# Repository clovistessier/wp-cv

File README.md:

# Waaave_Pool Eurorack CV Interface Module
The Waaave_Pool Eurorack CV Interface Module is a Eurorack module that allows you to use control voltage from a Eurorack modular synthesizer to modulate any of the 16 continuous parameters of the Waaave_Pool video synthesis system. Use CV from LFOs, sequencers, envelopes, S+H, and more to animate your video feedback. Used in conjuction with a conventional Eurorack synth patch, you can achieve nuanced syncing between your audio and video for a cohesive audiovisual performance. Due to the framebuffer based implementation of Waaave_Pool, the best visual results are using CV that changes at a speed lower than the framerate of the system.

## Revision B.
This version of the module connects directly to the GPIO pins of the Raspberry Pi 3B+ running Waaave_Pool. A limited run of these modules was produced and sold in August 2020. This version is intended to be used with LZX compatible eurorack modules and complies with the [LZX Patchable Video Standard](https://community.lzxindustries.net/t/the-lzx-patchable-video-standard/842) for "Animation Speed" CV (<30Hz), whereas +/-1V corresponds to +/-100% of the parameters range.
### Features
- 16 CV inputs expecting +/-1V (+/-12V tolerant)
- Bipolar attenuator aka attenuverter (-n to n) on each input
- Positive and Negative clipping for voltages outside the expected range
### Usage
All of the files required to build your own are included. You can upload the zipped gerber files to your PCB manufacturer of choice (JLCPCB has been used successfully in the past). Ordering an SMT stencil with the board is highly recommended due to the large quantity of SMD components. 

The KiCAD project files are also included, open the .pro file with KiCAD to view the project.

[Mouser Project Link](https://www.mouser.com/ProjectManager/ProjectDetail.aspx?AccessID=e002599eb7) for easy parts ordering. Don't forget the knobs and jacks from [Thonk](thonk.co.uk)!

The included front panel gerber files can be used to order an FR-4 front panel at the same time as the PCBs. You may get a follow up email from the PCB manufacturer since they assume that a PCB with no copper traces is probably unintentional.

To use the module with Waaave_Pool, you will need a 40-Pin IDC ribbon cable to connect betweent the header at the bottom of the module and the GPIO header of the Raspberry Pi. You will also need to be running a CV-compatible firmware version, which can be found all the way at the bottom of the [VSERPI Hardware and Images page](https://andreijaycreativecoding.com/VSERPI-hardware-and-images).

## Revision C. (WIP)
This version of the module incorporates an ESP32 microcontroller to handle the analog to digital conversion, and trasmits the information using [OSC](https://ccrma.stanford.edu/groups/osc/index.html) to Waaave_Pool over Ethernet and/or Wi-Fi. This version is intended to work with +/-5V control voltage, allowing for a much wider range of compatible CV sources from the Eurorack world, beyond just LZX. Due to the inherent flexibility of OSC, this module could also be used to send CV information to something other than Waaave_Pool, such as an application running on your computer. Development is still ongoing.

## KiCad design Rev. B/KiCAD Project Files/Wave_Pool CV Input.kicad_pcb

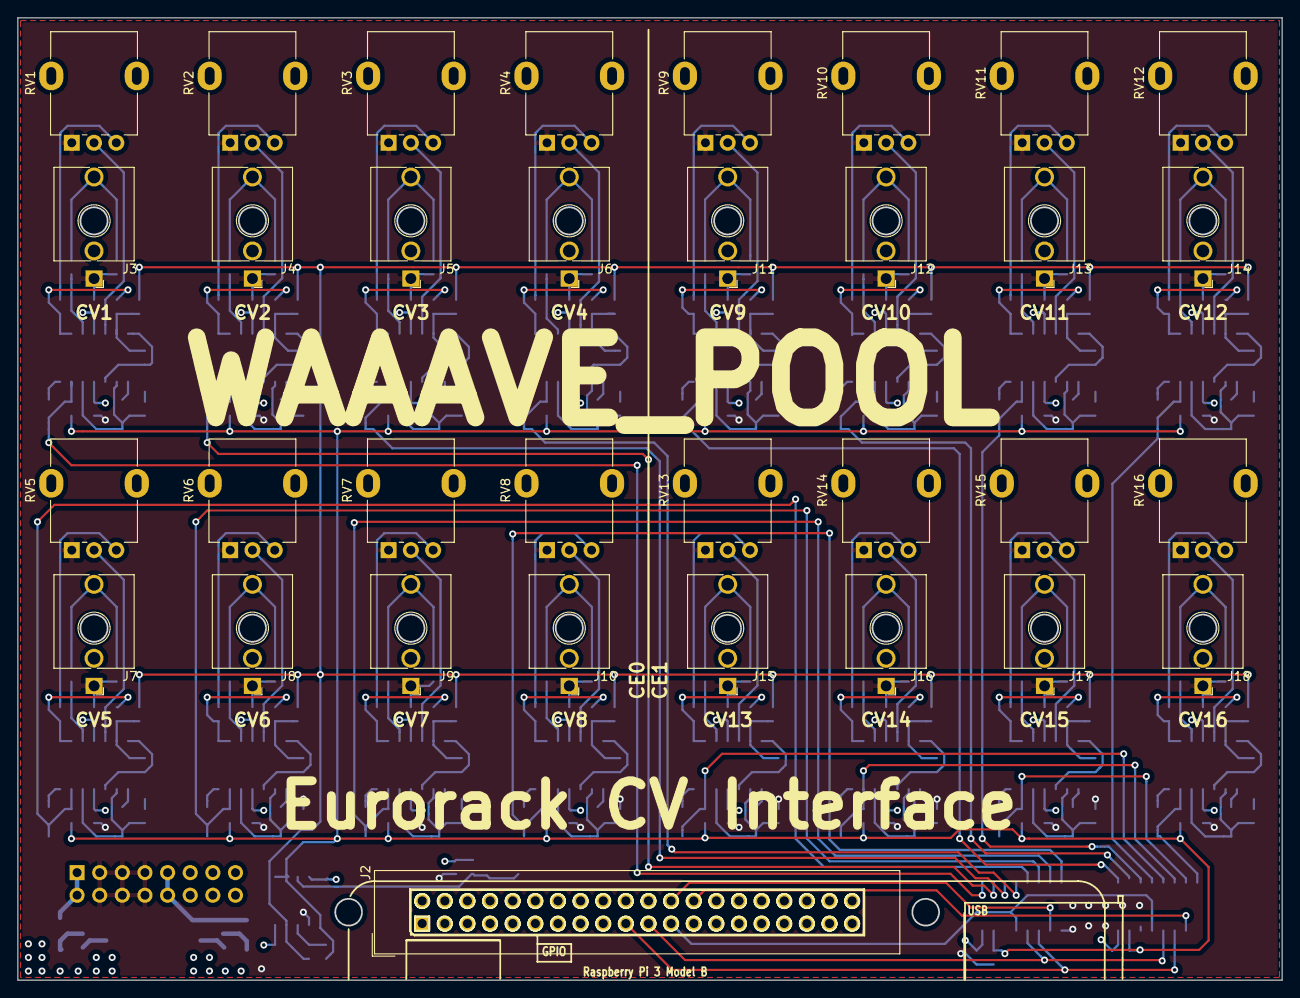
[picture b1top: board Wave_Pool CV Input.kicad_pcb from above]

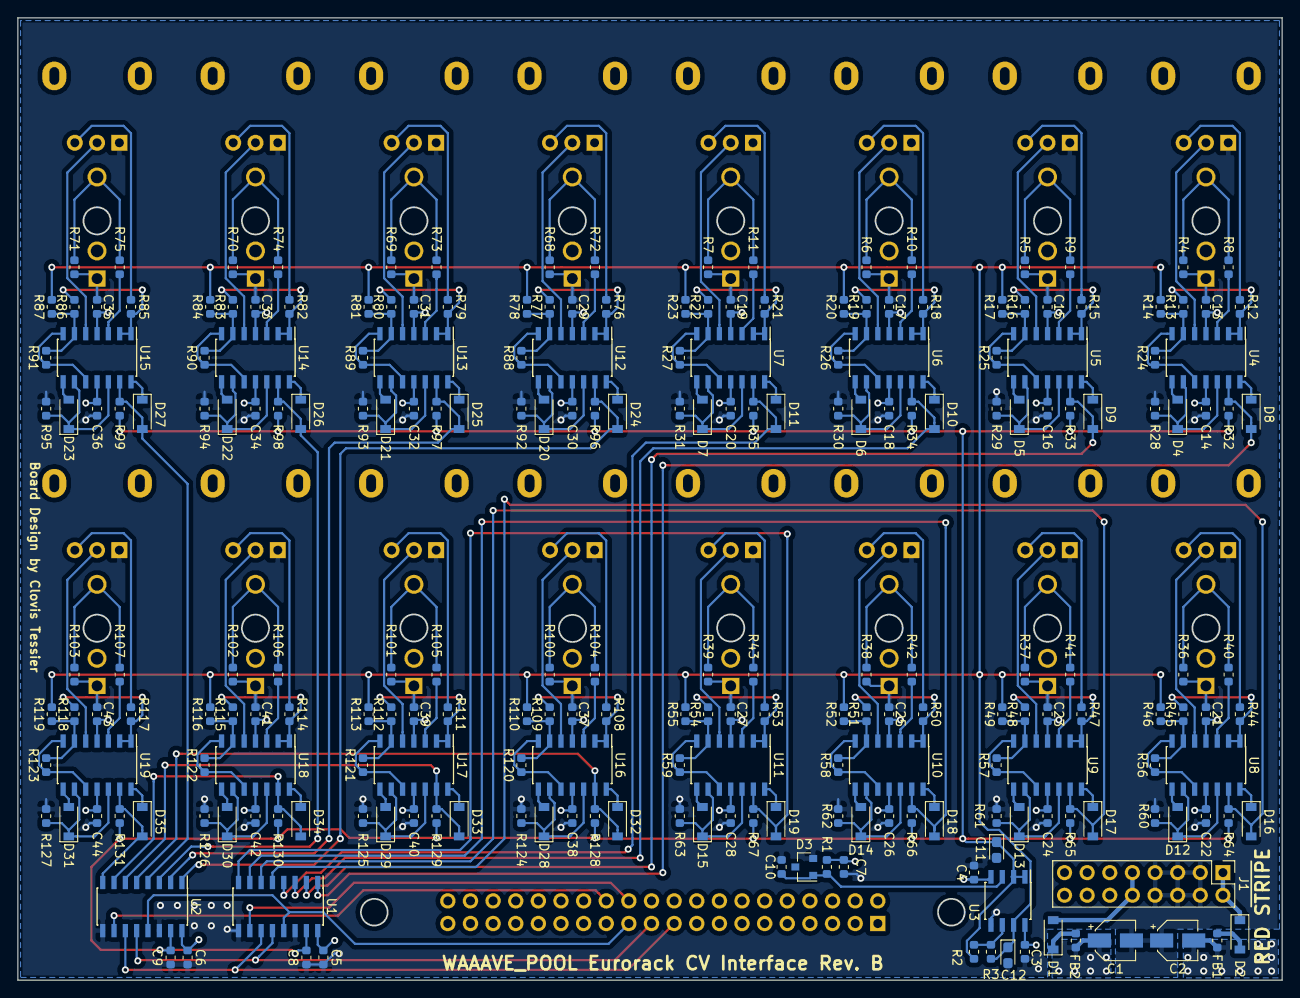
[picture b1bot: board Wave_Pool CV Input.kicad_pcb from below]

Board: 4 copper layers, 141.9 x 108.0 mm, 265 parts (232 on the bottom side), 193 nets.

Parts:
C1, C2: 10u 25V; CP_Elec_4x5.4
C3, C4, C5, C6, C8, C9, C13, C14, C15, C16, C17, C18, C19, C20, C21, C22, C23, C24, C25, C26, C27, C28, C29, C30, C31, C32, C33, C34, C35, C36, C37, C38, C39, C40, C41, C42, C43, C44: 100n; C_0603_1608Metric
C7, C10: 1u; C_0603_1608Metric
C11, C12: 10u; CP_EIA-2012-15_AVX-P
D1, D2: SM4001; D_SOD-123
D3: LM4040DBZ-2.0; SOT-23
D4, D5, D6, D7, D8, D9, D10, D11, D12, D13, D14, D15, D16, D17, D18, D19, D20, D21, D22, D23, D24, D25, D26, D27, D28, D29, D30, D31, D32, D33, D34, D35: 1N4148W; D_SOD-123
FB1, FB2: Ferrite_Bead; L_0603_1608Metric
J1: Eurorack_Power_Header_02x08_Hidden_Pins; PinHeader_2x08_P2.54mm_Vertical
J2: Raspberry_Pi_2_3; IDC-Header_2x20_P2.54mm_Vertical
J3, J4, J5, J6, J7, J8, J9, J10, J11, J12, J13, J14, J15, J16, J17, J18: Thonkiconn_Mono; Jack_3.5mm_QingPu_WQP-PJ398SM_Vertical_CircularHoles_Number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
R1, R2, R13, R14, R16, R17, R19, R20, R22, R23, R24, R25, R26, R27, R45, R46, R48, R49, R51, R52, R54, R55, R56, R57, R58, R59, R77, R78, R80, R81, R83, R84, R86, R87, R88, R89, R90, R91, R109, R110, R112, R113, R115, R116, R118, R119, R120, R121, R122, R123: 10K; R_0603_1608Metric
R3, R12, R15, R18, R21, R28, R29, R30, R31, R32, R33, R34, R35, R44, R47, R50, R53, R60, R61, R62, R63, R64, R65, R66, R67, R76, R79, R82, R85, R92, R93, R94, R95, R96, R97, R98, R99, R108, R111, R114, R117, R124, R125, R126, R127, R128, R129, R130, R131: 4.99K; R_0603_1608Metric
R4, R5, R6, R7, R36, R37, R38, R39, R68, R69, R70, R71, R100, R101, R102, R103: 100K; R_0603_1608Metric
R8, R9, R10, R11, R40, R41, R42, R43, R72, R73, R74, R75, R104, R105, R106, R107: 499R; R_0603_1608Metric
RV1, RV2, RV3, RV4, RV5, RV6, RV7, RV8, RV9, RV10, RV11, RV12, RV13, RV14, RV15, RV16: 10K; Potentiometer_Alpha_RD901F-40-00D_Single_Vertical
U1, U2: MCP3008; SOIC-16_3.9x9.9mm_P1.27mm
U3: TL072; SOIC-8_3.9x4.9mm_P1.27mm
U4, U5, U6, U7, U8, U9, U10, U11, U12, U13, U14, U15, U16, U17, U18, U19: TL074; SOIC-14_3.9x8.7mm_P1.27mm

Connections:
+3V3: C5.1, C6.1, J2.17, U1.16, U2.16
+12V: C1.1, C3.1, C7.1, C13.1, C15.1, C17.1, C19.1, C21.1, C23.1, C25.1, C27.1, C29.1, C31.1, C33.1, C35.1, C37.1, C39.1, C41.1, C43.1, FB2.1, R1.2, U3.8, U4.4, U5.4, U6.4, U7.4, U8.4, U9.4, U10.4, U11.4, U12.4, U13.4, U14.4, U15.4, U16.4, U17.4, U18.4, U19.4
-12V: C2.2, C4.2, C14.2, C16.2, C18.2, C20.2, C22.2, C24.2, C26.2, C28.2, C30.2, C32.2, C34.2, C36.2, C38.2, C40.2, C42.2, C44.2, FB1.1, U3.4, U4.11, U5.11, U6.11, U7.11, U8.11, U9.11, U10.11, U11.11, U12.11, U13.11, U14.11, U15.11, U16.11, U17.11, U18.11, U19.11
/CV Input 1-4/CV1: D8.2, R32.2, U1.1, U4.13
/CV Input 1-4/CV2: D9.2, R33.2, U1.2, U5.13
/CV Input 1-4/CV3: D10.2, R34.2, U1.3, U6.13
/CV Input 1-4/CV4: D11.2, R35.2, U1.4, U7.13
/CV Input 5-8/CV5: D16.2, R64.2, U1.5, U8.13
/CV Input 5-8/CV6: D17.2, R65.2, U1.6, U9.13
/CV Input 5-8/CV7: D18.2, R66.2, U1.7, U10.13
/CV Input 5-8/CV8: D19.2, R67.2, U1.8, U11.13
/CV Input 9-12/CV9: D24.2, R96.2, U2.1, U12.13
/CV Input 9-12/CV10: D25.2, R97.2, U2.2, U13.13
/CV Input 9-12/CV11: D26.2, R98.2, U2.3, U14.13
/CV Input 9-12/CV12: D27.2, R99.2, U2.4, U15.13
/CV Input 13-16/CV13: D32.2, R128.2, U2.5, U16.13
/CV Input 13-16/CV14: D33.2, R129.2, U2.6, U17.13
/CV Input 13-16/CV15: D34.2, R130.2, U2.7, U18.13
/CV Input 13-16/CV16: D35.2, R131.2, U2.8, U19.13
/SPI_CE0: J2.24, U1.10
/SPI_CE1: J2.26, U2.10
/SPI_CLK: J2.23, U1.13, U2.13
/SPI_MISO: J2.21, U1.12, U2.12
/SPI_MOSI: J2.19, U1.11, U2.11
/VREF_UNBUFFERED: C10.1, D3.1, R1.1, U3.3
DC_Offset: C12.1, R3.1, R14.2, R17.2, R20.2, R23.2, R46.2, R49.2, R52.2, R55.2, R78.2, R81.2, R84.2, R87.2, R110.2, R113.2, R116.2, R119.2, U3.7
GND: C1.2, C2.1, C3.2, C4.1, C5.2, C6.2, C7.2, C8.2, C9.2, C10.2, C11.2, C12.2, C13.2, C14.1, C15.2, C16.1, C17.2, C18.1, C19.2, C20.1, C21.2, C22.1, C23.2, C24.1, C25.2, C26.1, C27.2, C28.1, C29.2, C30.1, C31.2, C32.1, C33.2, C34.1, C35.2, C36.1, C37.2, C38.1, C39.2, C40.1, C41.2, C42.1, C43.2, C44.1, D3.2, J1.3, J1.4, J1.5, J1.6, J1.7, J1.8, J2.25, J3.1, J4.1, J5.1, J6.1, J7.1, J8.1, J9.1, J10.1, J11.1, J12.1, J13.1, J14.1, J15.1, J16.1, J17.1, J18.1, R4.2, R5.2, R6.2, R7.2, R28.1, R29.1, R30.1, R31.1, R36.2, R37.2, R38.2, R39.2, R60.1, R61.1, R62.1, R63.1, R68.2, R69.2, R70.2, R71.2, R92.1, R93.1, R94.1, R95.1, R100.2, R101.2, R102.2, R103.2, R124.1, R125.1, R126.1, R127.1, RV1.1, RV2.1, RV3.1, RV4.1, RV5.1, RV6.1, RV7.1, RV8.1, RV9.1, RV10.1, RV11.1, RV12.1, RV13.1, RV14.1, RV15.1, RV16.1, U1.9, U1.14, U2.9, U2.14, U3.5
unnamed: D1.1, FB2.2
unnamed: D1.2, J1.9, J1.10
unnamed: D2.1, J1.1, J1.2
unnamed: D2.2, FB1.2
unnamed: D4.1, R28.2, U4.9, U4.12
unnamed: D4.2, U4.8
unnamed: D5.1, R29.2, U5.9, U5.12
unnamed: D5.2, U5.8
unnamed: D6.1, R30.2, U6.9, U6.12
unnamed: D6.2, U6.8
unnamed: D7.1, R31.2, U7.9, U7.12
unnamed: D7.2, U7.8
unnamed: D8.1, U4.14
unnamed: D9.1, U5.14
unnamed: D10.1, U6.14
unnamed: D11.1, U7.14
unnamed: D12.1, R60.2, U8.9, U8.12
unnamed: D12.2, U8.8
unnamed: D13.1, R61.2, U9.9, U9.12
unnamed: D13.2, U9.8
unnamed: D14.1, R62.2, U10.9, U10.12
unnamed: D14.2, U10.8
unnamed: D15.1, R63.2, U11.9, U11.12
unnamed: D15.2, U11.8
unnamed: D16.1, U8.14
unnamed: D17.1, U9.14
unnamed: D18.1, U10.14
unnamed: D19.1, U11.14
unnamed: D20.1, R92.2, U12.9, U12.12
unnamed: D20.2, U12.8
unnamed: D21.1, R93.2, U13.9, U13.12
unnamed: D21.2, U13.8
unnamed: D22.1, R94.2, U14.9, U14.12
unnamed: D22.2, U14.8
unnamed: D23.1, R95.2, U15.9, U15.12
unnamed: D23.2, U15.8
unnamed: D24.1, U12.14
unnamed: D25.1, U13.14
unnamed: D26.1, U14.14
unnamed: D27.1, U15.14
unnamed: D28.1, R124.2, U16.9, U16.12
unnamed: D28.2, U16.8
unnamed: D29.1, R125.2, U17.9, U17.12
unnamed: D29.2, U17.8
unnamed: D30.1, R126.2, U18.9, U18.12
unnamed: D30.2, U18.8
unnamed: D31.1, R127.2, U19.9, U19.12
unnamed: D31.2, U19.8
unnamed: D32.1, U16.14
unnamed: D33.1, U17.14
unnamed: D34.1, U18.14
unnamed: D35.1, U19.14
unnamed: J3.3, R4.1, R8.2
unnamed: J4.3, R5.1, R9.2
unnamed: J5.3, R6.1, R10.2
unnamed: J6.3, R7.1, R11.2
unnamed: J7.3, R36.1, R40.2
unnamed: J8.3, R37.1, R41.2
unnamed: J9.3, R38.1, R42.2
unnamed: J10.3, R39.1, R43.2
unnamed: J11.3, R68.1, R72.2
unnamed: J12.3, R69.1, R73.2
unnamed: J13.3, R70.1, R74.2
unnamed: J14.3, R71.1, R75.2
unnamed: J15.3, R100.1, R104.2
unnamed: J16.3, R101.1, R105.2
unnamed: J17.3, R102.1, R106.2
unnamed: J18.3, R103.1, R107.2
unnamed: R2.1, R3.2, U3.6
unnamed: R8.1, U4.3
unnamed: R9.1, U5.3
unnamed: R10.1, U6.3
unnamed: R11.1, U7.3
unnamed: R12.1, RV1.3
unnamed: R12.2, R13.2, U4.1, U4.2
unnamed: R13.1, R14.1, R24.2, U4.6
unnamed: R15.1, RV2.3
unnamed: R15.2, R16.2, U5.1, U5.2
unnamed: R16.1, R17.1, R25.2, U5.6
unnamed: R18.1, RV3.3
unnamed: R18.2, R19.2, U6.1, U6.2
unnamed: R19.1, R20.1, R26.2, U6.6
unnamed: R21.1, RV4.3
unnamed: R21.2, R22.2, U7.1, U7.2
unnamed: R22.1, R23.1, R27.2, U7.6
unnamed: R24.1, U4.7, U4.10
unnamed: R25.1, U5.7, U5.10
unnamed: R26.1, U6.7, U6.10
unnamed: R27.1, U7.7, U7.10
unnamed: R40.1, U8.3
unnamed: R41.1, U9.3
unnamed: R42.1, U10.3
unnamed: R43.1, U11.3
unnamed: R44.1, RV5.3
unnamed: R44.2, R45.2, U8.1, U8.2
unnamed: R45.1, R46.1, R56.2, U8.6
unnamed: R47.1, RV6.3
unnamed: R47.2, R48.2, U9.1, U9.2
unnamed: R48.1, R49.1, R57.2, U9.6
unnamed: R50.1, RV7.3
unnamed: R50.2, R51.2, U10.1, U10.2
unnamed: R51.1, R52.1, R58.2, U10.6
unnamed: R53.1, RV8.3
unnamed: R53.2, R54.2, U11.1, U11.2
unnamed: R54.1, R55.1, R59.2, U11.6
unnamed: R56.1, U8.7, U8.10
unnamed: R57.1, U9.7, U9.10
unnamed: R58.1, U10.7, U10.10
unnamed: R59.1, U11.7, U11.10
unnamed: R72.1, U12.3
unnamed: R73.1, U13.3
unnamed: R74.1, U14.3
unnamed: R75.1, U15.3
unnamed: R76.1, RV9.3
unnamed: R76.2, R77.2, U12.1, U12.2
unnamed: R77.1, R78.1, R88.2, U12.6
unnamed: R79.1, RV10.3
unnamed: R79.2, R80.2, U13.1, U13.2
unnamed: R80.1, R81.1, R89.2, U13.6
unnamed: R82.1, RV11.3
unnamed: R82.2, R83.2, U14.1, U14.2
unnamed: R83.1, R84.1, R90.2, U14.6
unnamed: R85.1, RV12.3
unnamed: R85.2, R86.2, U15.1, U15.2
unnamed: R86.1, R87.1, R91.2, U15.6
unnamed: R88.1, U12.7, U12.10
unnamed: R89.1, U13.7, U13.10
unnamed: R90.1, U14.7, U14.10
unnamed: R91.1, U15.7, U15.10
unnamed: R104.1, U16.3
unnamed: R105.1, U17.3
unnamed: R106.1, U18.3
unnamed: R107.1, U19.3
unnamed: R108.1, RV13.3
unnamed: R108.2, R109.2, U16.1, U16.2
unnamed: R109.1, R110.1, R120.2, U16.6
unnamed: R111.1, RV14.3
unnamed: R111.2, R112.2, U17.1, U17.2
unnamed: R112.1, R113.1, R121.2, U17.6
unnamed: R114.1, RV15.3
unnamed: R114.2, R115.2, U18.1, U18.2
unnamed: R115.1, R116.1, R122.2, U18.6
unnamed: R117.1, RV16.3
unnamed: R117.2, R118.2, U19.1, U19.2
unnamed: R118.1, R119.1, R123.2, U19.6
unnamed: R120.1, U16.7, U16.10
unnamed: R121.1, U17.7, U17.10
unnamed: R122.1, U18.7, U18.10
unnamed: R123.1, U19.7, U19.10
unnamed: RV1.2, U4.5
unnamed: RV2.2, U5.5
unnamed: RV3.2, U6.5
unnamed: RV4.2, U7.5
unnamed: RV5.2, U8.5
unnamed: RV6.2, U9.5
unnamed: RV7.2, U10.5
unnamed: RV8.2, U11.5
unnamed: RV9.2, U12.5
unnamed: RV10.2, U13.5
unnamed: RV11.2, U14.5
unnamed: RV12.2, U15.5
unnamed: RV13.2, U16.5
unnamed: RV14.2, U17.5
unnamed: RV15.2, U18.5
unnamed: RV16.2, U19.5
Vref: C8.1, C9.1, C11.1, R2.2, R32.1, R33.1, R34.1, R35.1, R64.1, R65.1, R66.1, R67.1, R96.1, R97.1, R98.1, R99.1, R128.1, R129.1, R130.1, R131.1, U1.15, U2.15, U3.1, U3.2

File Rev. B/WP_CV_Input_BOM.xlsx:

Reference | Quantity | Value | Footprint | Vendor | Mouser P/N | Price | Ext. Price | Website | Description
C1 C2 | 2 | 10u 25V | Capacitor_THT:CP_Radial_D5.0mm_P2.00mm | Mouser | 667-ECE-A1VKS100 | 0.28000000000000003 | 0.56000000000000005 | https://www.mouser.com/ProductDetail/667-ECE-A1VKS100 | Aluminum Electrolytic Capacitors - Radial Leaded 10UF 35V KS RADIAL
C11 C12 | 2 | 10u | Capacitor_Tantalum_SMD:CP_EIA-2012-15_AVX-P | Mouser | 74-TMCP0J106MTRF | 0.36 | 0.72 | https://www.mouser.com/ProductDetail/74-TMCP0J106MTRF | Tantalum Capacitors - Solid SMD 7volts 10uF 20% Molded Case, 0805
C13 C14 C15 C16 C17 C18 C19 C20 C21 C22 C23 C24 C25 C26 C27 C28 C29 C3 C30 C31 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 | 38 | 100n | Capacitor_SMD:C_0603_1608Metric | Mouser | 80-C0603C104Z3V | 3.2000000000000001E-2 | 1.216 | https://www.mouser.com/ProductDetail/80-C0603C104Z3V | Multilayer Ceramic Capacitors MLCC - SMD/SMT 25V 0.1uF 0603 Y5V -20/+80%
C10 C7 | 2 | 1u | Capacitor_SMD:C_0603_1608Metric | Mouser | 80-C0603C105K9P | 0.1 | 0.2 | https://www.mouser.com/ProductDetail/80-C0603C105K9P | Multilayer Ceramic Capacitors MLCC - SMD/SMT 1uF 16.0V
D1 D2 | 2 | SM4001 | Diode_SMD:D_SOD-123 | Mouser | 833-SM4001PL-TP | 0.2 | 0.4 | https://www.mouser.com/ProductDetail/833-SM4001PL-TP | Rectifiers Standard 50V 1A
D3 | 1 | LM4040DBZ-2.0 | Package_TO_SOT_SMD:SOT-23 | Mouser | 700-LM4040AEM3-2.1T | 2.36 | 2.36 | https://www.mouser.com/ProductDetail/700-LM4040AEM3-2.1T | Voltage References Improved Precision Micropower Shunt Voltage Reference with M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
D10 D11 D12 D13 D14 D15 D16 D17 D18 D19 D20 D21 D22 D23 D24 D25 D26 D27 D28 D29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 | 32 | 1N4148W | Diode_SMD:D_SOD-123 | Mouser | 621-1N4148W-F | 0.16 | 5.12 | https://www.mouser.com/ProductDetail/621-1N4148W-F | Diodes - General Purpose, Power, Switching SURFACE MOUNT FAST SWITCHING DIODE
FB1 FB2 | 2 | Ferrite_Bead | Inductor_SMD:L_0603_1608Metric | Mouser | 875-MI0603J680R-10 | 0.1 | 0.2 | https://www.mouser.com/ProductDetail/875-MI0603J680R-10 | Ferrite Beads 68ohms 100MHz 1A Monolithic 0603 SMD
J1 | 1 | Eurorack_Power_Header_02x08 | Connector_PinHeader_2.54mm:PinHeader_2x08_P2.54mm_Vertical | Mouser | 649-1012938191601BLF | 0.48 | 0.48 | https://www.mouser.com/ProductDetail/649-1012938191601BLF | Headers & Wire Housings ECONOSTIK HEADER DR VT TH 2X8
J2 | 1 | Raspberry_Pi_2_3_GPIO_Header | Connector_PinHeader_2.54mm:PinHeader_2x20_P2.54mm_Vertical | Mouser | 649-1012938194002BLF | 1.1100000000000001 | 1.1100000000000001 | https://www.mouser.com/ProductDetail/649-1012938194002BLF | Headers & Wire Housings ECONOSTIK HEADER DR VT TH 2X20
R1 R109 R110 R112 R113 R115 R116 R118 R119 R120 R121 R122 R123 R13 R14 R16 R17 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 | 50 | 10K | Resistor_SMD:R_0603_1608Metric | Mouser | 667-ERJ-3EKF1002V | 0.05 | 2.5 | https://www.mouser.com/ProductDetail/667-ERJ-3EKF1002V | Thick Film Resistors - SMD 0603 10Kohms 1% AEC-Q200
R124 R125 R126 R127 R128 R129 R130 R131 R28 R29 R30 R31 R32 R33 R34 R35 R60 R61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 | 32 | 1K | Resistor_SMD:R_0603_1608Metric | Mouser | 667-ERJ-PA3F1001V | 0.06 | 1.92 | https://www.mouser.com/ProductDetail/667-ERJ-PA3F1001V | Thick Film Resistors - SMD 0603 1Kohm 1% Anti-Surge AEC-Q200
R108 R111 R114 R117 R12 R15 R18 R21 R3 R44 R47 R50 R53 R76 R79 R82 R85 | 17 | 4.99K | Resistor_SMD:R_0603_1608Metric | Mouser | 603-RC0603FR-104K99L | 0.02 | 0.34 | https://www.mouser.com/ProductDetail/603-RC0603FR-104K99L | Thick Film Resistors - SMD 4.99K ohm 1% 75V General Purpose
R100 R101 R102 R103 R36 R37 R38 R39 R4 R5 R6 R68 R69 R7 R70 R71 | 16 | 100K | Resistor_SMD:R_0603_1608Metric | Mouser | 603-RC0603FR-07100KL | 0.02 | 0.32 | https://www.mouser.com/ProductDetail/603-RC0603FR-07100KL | Thick Film Resistors - SMD 100K OHM 1%
R10 R104 R105 R106 R107 R11 R40 R41 R42 R43 R72 R73 R74 R75 R8 R9 | 16 | 499R | Resistor_SMD:R_0603_1608Metric | Mouser | 71-CRCW0603-499-E3 | 0.03 | 0.48 | https://www.mouser.com/ProductDetail/71-CRCW0603-499-E3 | Thick Film Resistors - SMD 1/10watt 499ohms 1%
U1 U2 | 2 | MCP3008 | Package_SO:SOIC-16_3.9x9.9mm_P1.27mm | Mouser | 579-MCP3008T-I/SL | 2.19 | 4.38 | https://www.mouser.com/ProductDetail/579-MCP3008T-I-SL | Analog to Digital Converters - ADC 10-bit SPI 8 Chl IND TEMP, SOIC16
U3 | 1 | TL072 | Package_SO:SOIC-8_3.9x4.9mm_P1.27mm | Mouser | 595-TL072CDR | 0.41 | 0.41 | https://www.mouser.com/ProductDetail/595-TL072CDR | Operational Amplifiers - Op Amps Dual JFET Op Amp
U10 U11 U12 U13 U14 U15 U16 U17 U18 U19 U4 U5 U6 U7 U8 U9 | 16 | TL074 | Package_SO:SOIC-14_3.9x8.7mm_P1.27mm | Mouser | 511-TL074IDT | 0.48 | 7.68 | https://www.mouser.com/ProductDetail/511-TL074IDT | Operational Amplifiers - Op Amps Quad Low Noise JFET
J10 J11 J12 J13 J14 J15 J16 J17 J18 J3 J4 J5 J6 J7 J8 J9 | 16 | Thonkiconn_Mono | Connector_Audio_Extra:Jack_3.5mm_QingPu_WQP-PJ398SM_Vertical_CircularHoles_Numb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 | Thonk |  | 0.43 | 6.88 | https://www.thonk.co.uk/shop/thonkiconn/ | Thonkiconn Mono 3.5mm Audio Jack
RV1 RV10 RV11 RV12 RV13 RV14 RV15 RV16 RV2 RV3 RV4 RV5 RV6 RV7 RV8 RV9 | 16 | B10K Center Detent | Potentiometer_THT_Extra:Potentiometer_Alpha_RD901F-40-00D_Single_Vertical_Circu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 | Thonk |  | 1.04 | 16.64 | https://www.thonk.co.uk/shop/ttpots/ | Song Huei 9mm Tall Trimmer Potentiometer
 |  |  |  |  |  | Total Price: | 53.916000000000004
 |  |  |  |  |  |  |  | Mouser Project Page:
 |  |  |  |  |  |  |  | https://www.mouser.com/ProjectManager/ProjectDetail.aspx?Acc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

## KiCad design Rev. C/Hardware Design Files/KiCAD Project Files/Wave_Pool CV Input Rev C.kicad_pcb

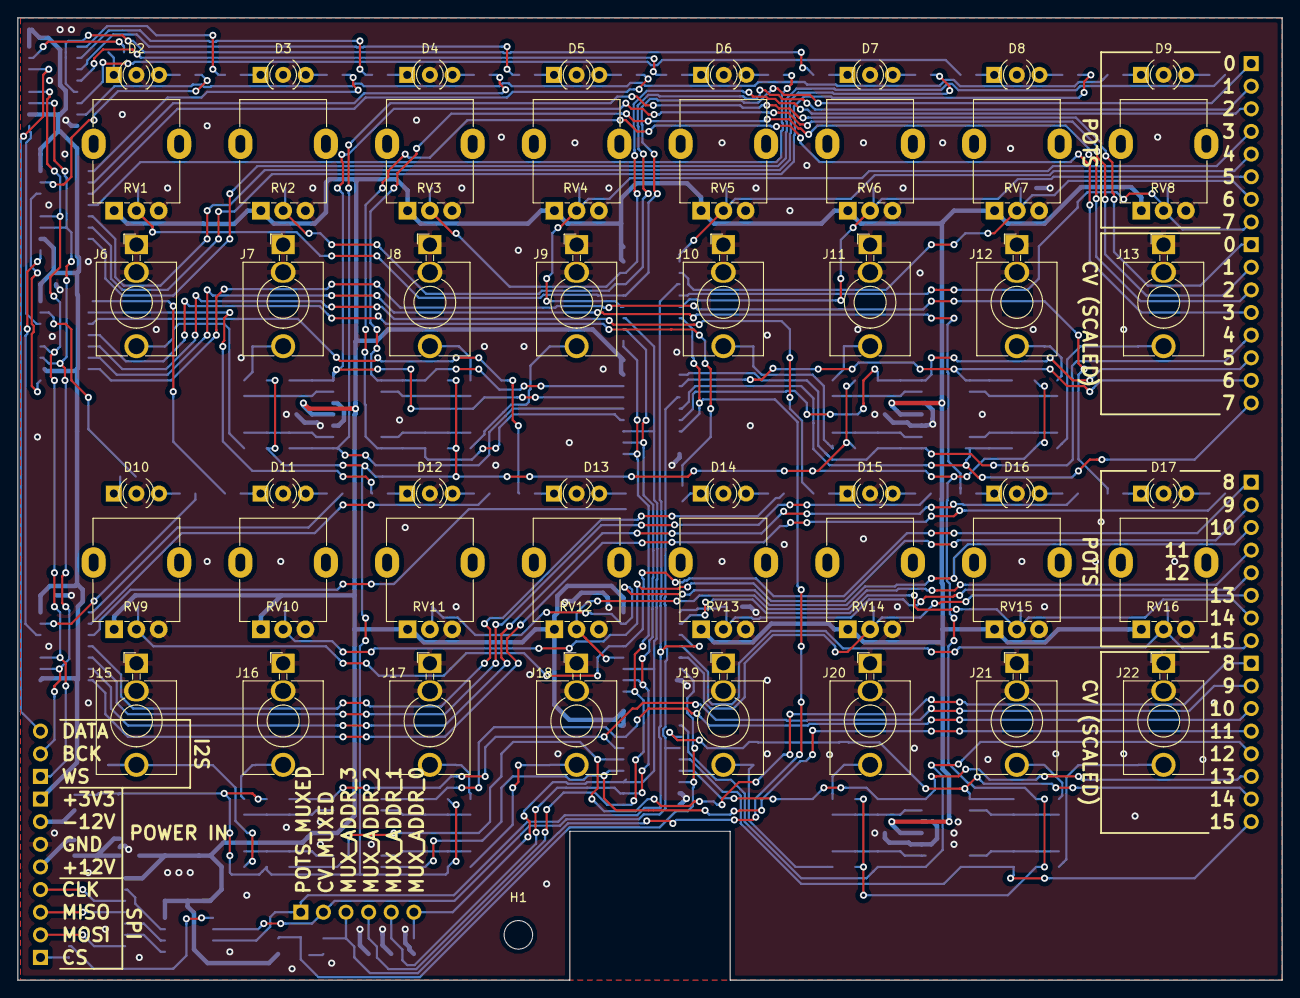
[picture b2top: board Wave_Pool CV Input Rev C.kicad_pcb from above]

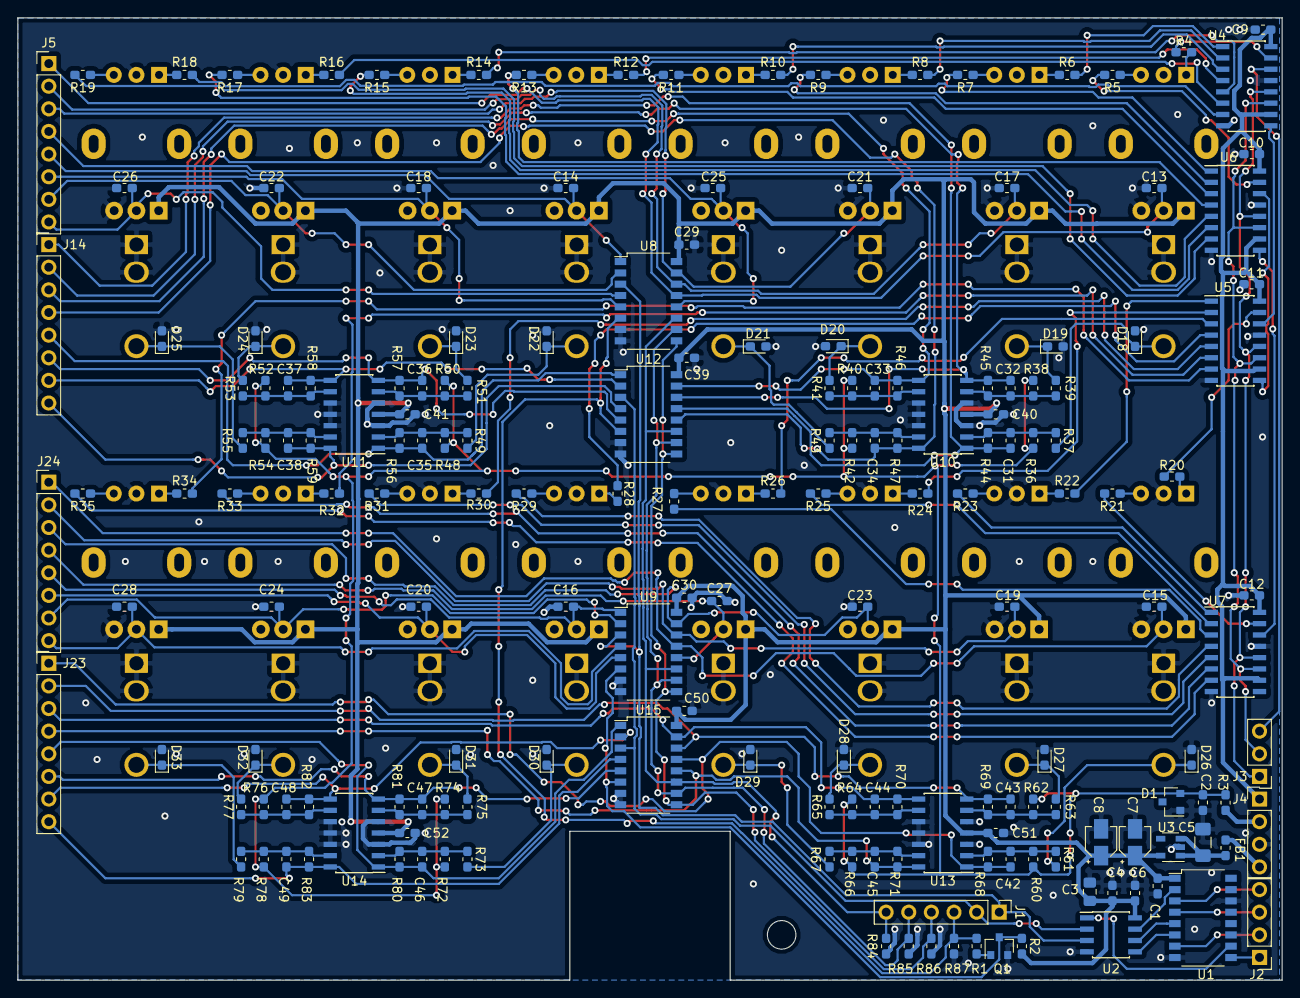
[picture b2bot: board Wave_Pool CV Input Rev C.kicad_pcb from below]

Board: 2 copper layers, 141.9 x 108.0 mm, 230 parts (181 on the bottom side), 157 nets.

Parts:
C1, C6, C9, C10, C11, C12, C13, C14, C15, C16, C17, C18, C19, C20, C21, C22, C23, C24, C25, C26, C27, C28, C29, C30, C39, C40, C41, C50, C51, C52: 100n; C_0603_1608Metric_Pad1.05x0.95mm_HandSolder
C2, C4: 1u; C_0603_1608Metric_Pad1.05x0.95mm_HandSolder
C3: 10u; C_0805_2012Metric_Pad1.15x1.40mm_HandSolder
C5: 22u; C_1206_3216Metric_Pad1.42x1.75mm_HandSolder
C7, C8: 10u; CP_Elec_3x5.4
C31, C32, C33, C34, C35, C36, C37, C38, C42, C43, C44, C45, C46, C47, C48, C49: 1n; C_0603_1608Metric_Pad1.05x0.95mm_HandSolder
D1: LM4040DBZ-10; SOT-23
D2, D3, D4, D5, D6, D7, D8, D9, D10, D11, D12, D13, D14, D15, D16, D17: Kingbright W115WSURKMGKW; LED_D3.0mm-3
D18, D19, D20, D21, D22, D23, D24, D25, D26, D27, D28, D29, D30, D31, D32, D33: D_TVS; D_0603_1608Metric_Pad1.05x0.95mm_HandSolder
FB1: Ferrite_Bead; L_0603_1608Metric_Pad1.05x0.95mm_HandSolder
H1: MountingHole; MountingHole_3.2mm_M3
J1: Conn_01x06; PinHeader_1x06_P2.54mm_Vertical
J2, J4: Conn_01x04; PinHeader_1x04_P2.54mm_Vertical
J3: Conn_01x03; PinHeader_1x03_P2.54mm_Vertical
J5, J14, J23, J24: Conn_01x08; PinHeader_1x08_P2.54mm_Vertical
J6, J7, J8, J9, J10, J11, J12, J13, J15, J16, J17, J18, J19, J20, J21, J22: Thonkiconn_Mono; Jack_3.5mm_Thonkiconn_Mono
Q1: MMBT3904; SOT-23
R1, R2, R84, R85, R86, R87: 10k; R_0603_1608Metric_Pad1.05x0.95mm_HandSolder
R3, R4, R6, R8, R10, R12, R14, R16, R18, R20, R22, R24, R26, R28, R30, R32, R34: 2.4k; R_0603_1608Metric_Pad1.05x0.95mm_HandSolder
R5, R7, R9, R11, R13, R15, R17, R19, R21, R23, R25, R27, R29, R31, R33, R35: 1.5k; R_0603_1608Metric_Pad1.05x0.95mm_HandSolder
R36, R38, R40, R42, R48, R50, R52, R54, R60, R62, R64, R66, R72, R74, R76, R78: 200k; R_0603_1608Metric_Pad1.05x0.95mm_HandSolder
R37, R39, R41, R43, R49, R51, R53, R55, R61, R63, R65, R67, R73, R75, R77, R79: 100k; R_0603_1608Metric_Pad1.05x0.95mm_HandSolder
R44, R45, R46, R47, R56, R57, R58, R59, R68, R69, R70, R71, R80, R81, R82, R83: 33k; R_0603_1608Metric_Pad1.05x0.95mm_HandSolder
RV1, RV2, RV3, RV4, RV5, RV6, RV7, RV8, RV9, RV10, RV11, RV12, RV13, RV14, RV15, RV16: R_POT_US; Potentiometer_Alpha_9mm_Single_Vertical
U1: 4050; SOP-16_4.4x10.4mm_P1.27mm
U2: MCP3202; SOIC-8_3.9x4.9mm_P1.27mm
U3: LD2981ABM33TR; SOT-23-5
U4, U5, U6, U7: 74HC595; SOIC-16_3.9x9.9mm_P1.27mm
U8, U9, U12, U15: 4051; SOP-16_4.4x10.4mm_P1.27mm
U10, U11, U13, U14: MCP6004; SOIC-14_3.9x8.7mm_P1.27mm

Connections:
+3.3VA: C1.1, C3.1, C4.1, C6.1, C7.1, C8.1, C29.1, C30.1, C39.1, C40.1, C41.1, C50.1, C51.1, C52.1, R2.2, RV1.1, RV2.1, RV3.1, RV4.1, RV5.1, RV6.1, RV7.1, RV8.1, RV9.1, RV10.1, RV11.1, RV12.1, RV13.1, RV14.1, RV15.1, RV16.1, U1.1, U2.8, U3.5, U8.16, U9.16, U10.4, U11.4, U12.16, U13.4, U14.4, U15.16
+3V3: C9.1, C10.1, C11.1, C12.1, J4.1, U4.10, U4.16, U5.10, U5.16, U6.10, U6.16, U7.10, U7.16
+12V: FB1.2, J4.4
-12V: J4.2, R3.1
/ATTENUVERTER_POTS/CV_ATT_0: C13.1, J5.1, RV1.2, U8.13
/ATTENUVERTER_POTS/CV_ATT_1: C17.1, J5.2, RV2.2, U8.14
/ATTENUVERTER_POTS/CV_ATT_2: C21.1, J5.3, RV3.2, U8.15
/ATTENUVERTER_POTS/CV_ATT_3: C25.1, J5.4, RV4.2, U8.12
/ATTENUVERTER_POTS/CV_ATT_4: C14.1, J5.5, RV5.2, U8.1
/ATTENUVERTER_POTS/CV_ATT_5: C18.1, J5.6, RV6.2, U8.5
/ATTENUVERTER_POTS/CV_ATT_6: C22.1, J5.7, RV7.2, U8.2
/ATTENUVERTER_POTS/CV_ATT_7: C26.1, J5.8, RV8.2, U8.4
/ATTENUVERTER_POTS/CV_ATT_8: C15.1, J24.1, RV9.2, U9.13
/ATTENUVERTER_POTS/CV_ATT_9: C19.1, J24.2, RV10.2, U9.14
/ATTENUVERTER_POTS/CV_ATT_10: C23.1, J24.3, RV11.2, U9.15
/ATTENUVERTER_POTS/CV_ATT_11: C27.1, J24.4, RV12.2, U9.12
/ATTENUVERTER_POTS/CV_ATT_12: C16.1, J24.5, RV13.2, U9.1
/ATTENUVERTER_POTS/CV_ATT_13: C20.1, J24.6, RV14.2, U9.5
/ATTENUVERTER_POTS/CV_ATT_14: C24.1, J24.7, RV15.2, U9.2
/ATTENUVERTER_POTS/CV_ATT_15: C28.1, J24.8, RV16.2, U9.4
/CV_ATT_MUXED: J1.1, U2.3, U8.3, U9.3
/CV_INPUTS/CV_INPUTS_BOTTOM_ROW/CV_IN_8: C42.1, J23.1, R68.1, U13.1, U15.13
/CV_INPUTS/CV_INPUTS_BOTTOM_ROW/CV_IN_9: C43.1, J23.2, R69.1, U13.7, U15.14
/CV_INPUTS/CV_INPUTS_BOTTOM_ROW/CV_IN_10: C44.1, J23.3, R70.1, U13.8, U15.15
/CV_INPUTS/CV_INPUTS_BOTTOM_ROW/CV_IN_11: C45.1, J23.4, R71.1, U13.14, U15.12
/CV_INPUTS/CV_INPUTS_BOTTOM_ROW/CV_IN_12: C46.1, J23.5, R80.1, U14.1, U15.1
/CV_INPUTS/CV_INPUTS_BOTTOM_ROW/CV_IN_13: C47.1, J23.6, R81.1, U14.7, U15.5
/CV_INPUTS/CV_INPUTS_BOTTOM_ROW/CV_IN_14: C48.1, J23.7, R82.1, U14.8, U15.2
/CV_INPUTS/CV_INPUTS_BOTTOM_ROW/CV_IN_15: C49.1, J23.8, R83.1, U14.14, U15.4
/CV_INPUTS/CV_INPUTS_TOP_ROW/CV_IN_0: C31.1, J14.1, R44.1, U10.1, U12.13
/CV_INPUTS/CV_INPUTS_TOP_ROW/CV_IN_1: C32.1, J14.2, R45.1, U10.7, U12.14
/CV_INPUTS/CV_INPUTS_TOP_ROW/CV_IN_2: C33.1, J14.3, R46.1, U10.8, U12.15
/CV_INPUTS/CV_INPUTS_TOP_ROW/CV_IN_3: C34.1, J14.4, R47.1, U10.14, U12.12
/CV_INPUTS/CV_INPUTS_TOP_ROW/CV_IN_4: C35.1, J14.5, R56.1, U11.1, U12.1
/CV_INPUTS/CV_INPUTS_TOP_ROW/CV_IN_5: C36.1, J14.6, R57.1, U11.7, U12.5
/CV_INPUTS/CV_INPUTS_TOP_ROW/CV_IN_6: C37.1, J14.7, R58.1, U11.8, U12.2
/CV_INPUTS/CV_INPUTS_TOP_ROW/CV_IN_7: C38.1, J14.8, R59.1, U11.14, U12.4
/CV_IN_MUXED: J1.2, U2.2, U12.3, U15.3
/I2S_BCK: J3.2, U4.11, U5.11, U6.11, U7.11
/I2S_DATA: J3.3, U4.14
/I2S_WS: J3.1, U4.12, U5.12, U6.12, U7.12
/LEDS/LED_G_0: R5.2, U6.15
/LEDS/LED_G_1: R7.2, U6.1
/LEDS/LED_G_2: R9.2, U6.2
/LEDS/LED_G_3: R11.2, U6.3
/LEDS/LED_G_4: R13.2, U6.4
/LEDS/LED_G_5: R15.2, U6.5
/LEDS/LED_G_6: R17.2, U6.6
/LEDS/LED_G_7: R19.2, U6.7
/LEDS/LED_G_8: R21.2, U7.15
/LEDS/LED_G_9: R23.2, U7.1
/LEDS/LED_G_10: R25.2, U7.2
/LEDS/LED_G_11: R27.2, U7.3
/LEDS/LED_G_12: R29.2, U7.4
/LEDS/LED_G_13: R31.2, U7.5
/LEDS/LED_G_14: R33.2, U7.6
/LEDS/LED_G_15: R35.2, U7.7
/LEDS/LED_R_0: R4.2, U4.15
/LEDS/LED_R_1: R6.2, U4.1
/LEDS/LED_R_2: R8.2, U4.2
/LEDS/LED_R_3: R10.2, U4.3
/LEDS/LED_R_4: R12.2, U4.4
/LEDS/LED_R_5: R14.2, U4.5
/LEDS/LED_R_6: R16.2, U4.6
/LEDS/LED_R_7: R18.2, U4.7
/LEDS/LED_R_8: R20.2, U5.15
/LEDS/LED_R_9: R22.2, U5.1
/LEDS/LED_R_10: R24.2, U5.2
/LEDS/LED_R_11: R26.2, U5.3
/LEDS/LED_R_12: R28.2, U5.4
/LEDS/LED_R_13: R30.2, U5.5
/LEDS/LED_R_14: R32.2, U5.6
/LEDS/LED_R_15: R34.2, U5.7
/MUX_ADDR_0: J1.6, R84.1, U8.11, U9.11, U12.11, U15.11
/MUX_ADDR_1: J1.5, R85.1, U8.10, U9.10, U12.10, U15.10
/MUX_ADDR_2: J1.4, R86.1, U8.9, U9.9, U12.9, U15.9
/MUX_ADDR_3: J1.3, R1.2, R87.1, U8.6, U12.6
/MUX_ADDR_3n: Q1.3, R2.1, U9.6, U15.6
/SPI_CLK: J2.4, U1.3
/SPI_CLK_BUF: U1.2, U2.7
/SPI_CS_ADC: J2.1, U1.9
/SPI_CS_ADC_BUF: U1.10, U2.1
/SPI_MISO: U1.5, U2.6
/SPI_MISO_BUF: J2.3, U1.4
/SPI_MOSI: J2.2, U1.7
/SPI_MOSI_BUF: U1.6, U2.5
AREF_-10: C2.1, D1.2, R3.2, R36.2, R38.2, R40.2, R42.2, R48.2, R50.2, R52.2, R54.2, R60.2, R62.2, R64.2, R66.2, R72.2, R74.2, R76.2, R78.2
GND: C1.2, C2.2, C3.2, C4.2, C5.2, C6.2, C7.2, C8.2, C9.2, C10.2, C11.2, C12.2, C13.2, C14.2, C15.2, C16.2, C17.2, C18.2, C19.2, C20.2, C21.2, C22.2, C23.2, C24.2, C25.2, C26.2, C27.2, C28.2, C29.2, C30.2, C39.2, C40.2, C41.2, C50.2, C51.2, C52.2, D1.1, D2.2, D3.2, D4.2, D5.2, D6.2, D7.2, D8.2, D9.2, D10.2, D11.2, D12.2, D13.2, D14.2, D15.2, D16.2, D17.2, D18.2, D19.2, D20.2, D21.2, D22.2, D23.2, D24.2, D25.2, D26.2, D27.2, D28.2, D29.2, D30.2, D31.2, D32.2, D33.2, J4.3, J6.1, J6.2, J7.1, J7.2, J8.1, J8.2, J9.1, J9.2, J10.1, J10.2, J11.1, J11.2, J12.1, J12.2, J13.1, J13.2, J15.1, J15.2, J16.1, J16.2, J17.1, J17.2, J18.1, J18.2, J19.1, J19.2, J20.1, J20.2, J21.1, J21.2, J22.1, J22.2, Q1.2, R84.2, R85.2, R86.2, R87.2, RV1.3, RV2.3, RV3.3, RV4.3, RV5.3, RV6.3, RV7.3, RV8.3, RV9.3, RV10.3, RV11.3, RV12.3, RV13.3, RV14.3, RV15.3, RV16.3, U1.8, U1.11, U1.14, U2.4, U3.2, U4.8, U4.13, U5.8, U5.13, U6.8, U6.13, U7.8, U7.13, U8.7, U8.8, U9.7, U9.8, U10.3, U10.5, U10.10, U10.11, U10.12, U11.3, U11.5, U11.10, U11.11, U11.12, U12.7, U12.8, U13.3, U13.5, U13.10, U13.11, U13.12, U14.3, U14.5, U14.10, U14.11, U14.12, U15.7, U15.8
unnamed: C5.1, FB1.1, U3.1, U3.3
unnamed: C31.2, R36.1, R37.1, R44.2, U10.2
unnamed: C32.2, R38.1, R39.1, R45.2, U10.6
unnamed: C33.2, R40.1, R41.1, R46.2, U10.9
unnamed: C34.2, R42.1, R43.1, R47.2, U10.13
unnamed: C35.2, R48.1, R49.1, R56.2, U11.2
unnamed: C36.2, R50.1, R51.1, R57.2, U11.6
unnamed: C37.2, R52.1, R53.1, R58.2, U11.9
unnamed: C38.2, R54.1, R55.1, R59.2, U11.13
unnamed: C42.2, R60.1, R61.1, R68.2, U13.2
unnamed: C43.2, R62.1, R63.1, R69.2, U13.6
unnamed: C44.2, R64.1, R65.1, R70.2, U13.9
unnamed: C45.2, R66.1, R67.1, R71.2, U13.13
unnamed: C46.2, R72.1, R73.1, R80.2, U14.2
unnamed: C47.2, R74.1, R75.1, R81.2, U14.6
unnamed: C48.2, R76.1, R77.1, R82.2, U14.9
unnamed: C49.2, R78.1, R79.1, R83.2, U14.13
unnamed: D2.1, R4.1
unnamed: D2.3, R5.1
unnamed: D3.1, R6.1
unnamed: D3.3, R7.1
unnamed: D4.1, R8.1
unnamed: D4.3, R9.1
unnamed: D5.1, R10.1
unnamed: D5.3, R11.1
unnamed: D6.1, R12.1
unnamed: D6.3, R13.1
unnamed: D7.1, R14.1
unnamed: D7.3, R15.1
unnamed: D8.1, R16.1
unnamed: D8.3, R17.1
unnamed: D9.1, R18.1
unnamed: D9.3, R19.1
unnamed: D10.1, R20.1
unnamed: D10.3, R21.1
unnamed: D11.1, R22.1
unnamed: D11.3, R23.1
unnamed: D12.1, R24.1
unnamed: D12.3, R25.1
unnamed: D13.1, R26.1
unnamed: D13.3, R27.1
unnamed: D14.1, R28.1
unnamed: D14.3, R29.1
unnamed: D15.1, R30.1
unnamed: D15.3, R31.1
unnamed: D16.1, R32.1
unnamed: D16.3, R33.1
unnamed: D17.1, R34.1
unnamed: D17.3, R35.1
unnamed: D18.1, J6.3, R37.2
unnamed: D19.1, J7.3, R39.2
unnamed: D20.1, J8.3, R41.2
unnamed: D21.1, J9.3, R43.2
unnamed: D22.1, J10.3, R49.2
unnamed: D23.1, J11.3, R51.2
unnamed: D24.1, J12.3, R53.2
unnamed: D25.1, J13.3, R55.2
unnamed: D26.1, J15.3, R61.2
unnamed: D27.1, J16.3, R63.2
unnamed: D28.1, J17.3, R65.2
unnamed: D29.1, J18.3, R67.2
unnamed: D30.1, J19.3, R73.2
unnamed: D31.1, J20.3, R75.2
unnamed: D32.1, J21.3, R77.2
unnamed: D33.1, J22.3, R79.2
unnamed: Q1.1, R1.1
unnamed: U4.9, U5.14
unnamed: U5.9, U6.14
unnamed: U6.9, U7.14

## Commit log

2020-09-11 nothing's working right now
2020-09-11 Added 2nd mcp and OSC, sampling less buggy now.
2020-09-11 comments and NULL to nullptr
2020-09-17 a little cleanup
2020-09-17 a little more cleanup
2020-09-25 Sending one UDP packet per param
2020-10-05 added OSC over Ethernet task.
2020-10-08 changed param vector to String C array
2021-01-15 added MCP3208 private library
2022-03-03 Added HW design files
    Added HW design files for Rev. B:
    -KiCAD project files
    -PCB gerber files for manufacturing
    -Front Panel gerber files for manufacturing
    -Schematic PDF
    -BOM with Mouser project link
2022-03-03 Added analog MUX logic and LED control
    updated analog read task to implement MUX switching logic
    Added LED control logic using I2S and shift registers
2022-03-03 deleted .travis.yml
